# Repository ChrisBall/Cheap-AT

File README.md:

# Cheap AT
 Repository for cheap Assistive Tech and Accessible Music Tech

 Currently seeking help to develop and improve these repositories.

 Switch Hub - Contains files necessary to reproduce an 8-input HID MIDI switch hub, based on the XIAO ESP32S3 dev board. This means you can connect accessibility switches to this box and plug it into your computer, and you'll get musical MIDI data when you press the attached switches.

 Quick Switch - A simple design for a 3D printed accessibility switch (developed in OpenSCAD) that is made of 3 parts: a top; a base; and a PCB. The design is extremely cheap & simple to manufacture, although could stand to be improved; the switch requires different levels of pressure depending on where you press it, and is not especially durable.

 Desired Improvements:
 
 - Multiple switch hub firmware types for different purposes (keyboard/gamepad/joystick emulation) with a simple user interface for configuration, or a single multipurpose firmware with easy configuration.
 - Cheaper hardware for the switch hub - I am currently using a XIAO ESP32S3 as it provides battery management and allows for future wireless/BLE versions, but there may be a cheaper dev board or bespoke hardware.

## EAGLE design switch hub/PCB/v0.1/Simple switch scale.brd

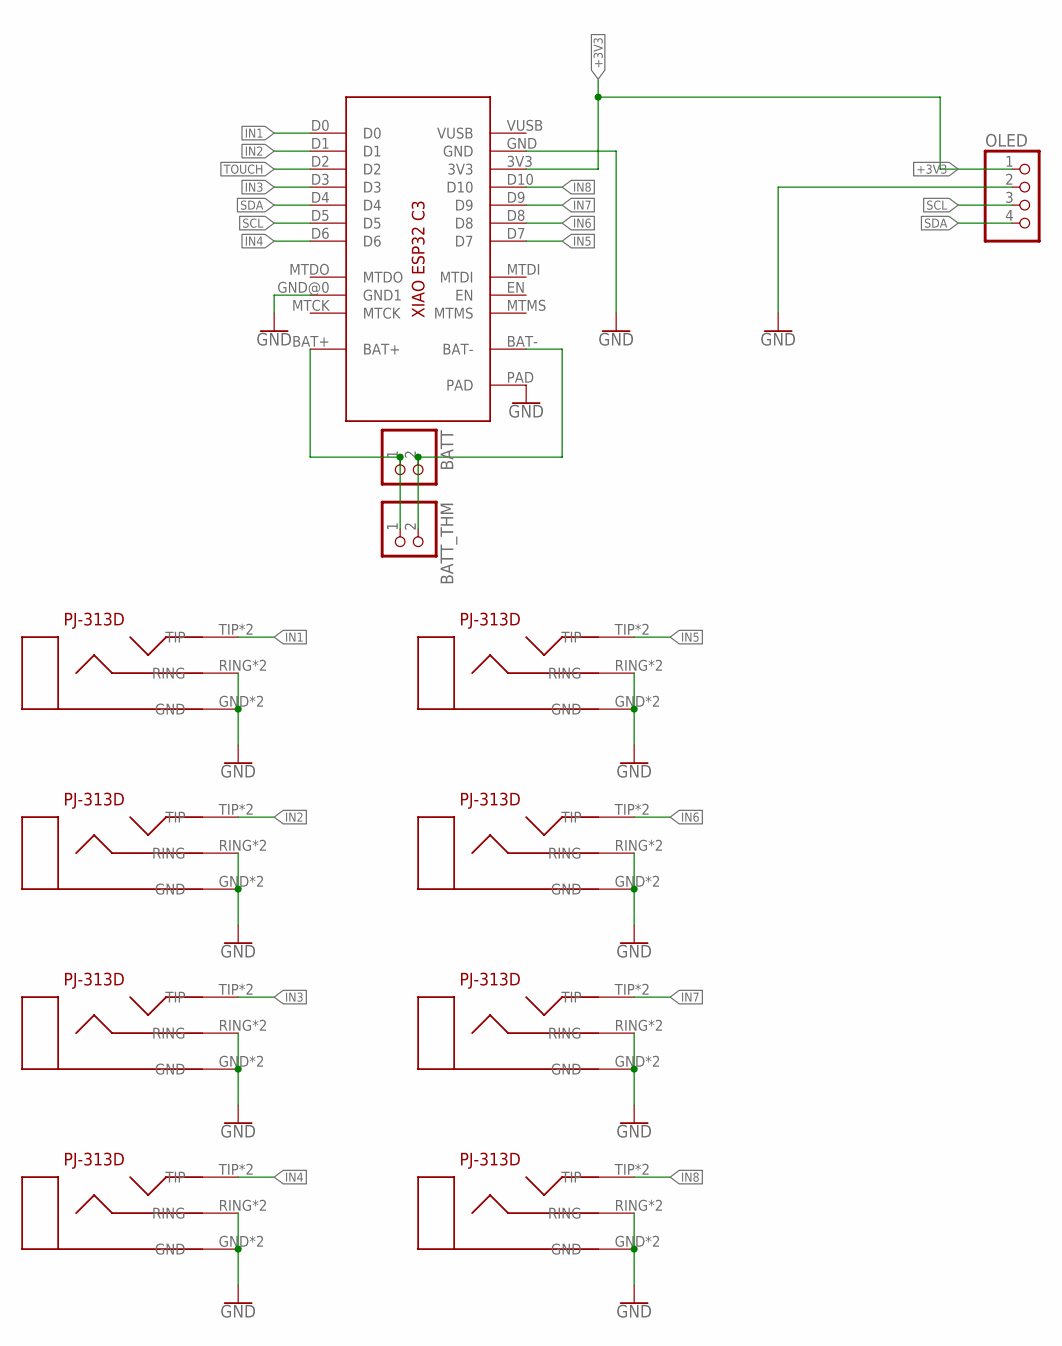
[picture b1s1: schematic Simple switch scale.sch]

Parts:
BATT: JST_2PIN-SMT-RA; JST-PH-2-SMT-RA
BATT_THM: JST_2PIN-THM-RA; JST-PH-2-THM-RA
IN1, IN2, IN3, IN4, IN5, IN6, IN7, IN8: 3.5MM_JACK; PJ-313D-SMT
OLED: HEADER-1X4; 1X04_OVAL
U$1: XIAO_ESP32C3_SMD

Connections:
+3V3: OLED.1, U$1.3V3
GND: IN1.GND, IN1.GND0 (GND), IN1.RING, IN1.RING0 (RING), IN2.GND, IN2.GND0 (GND), IN2.RING, IN2.RING0 (RING), IN3.GND, IN3.GND0 (GND), IN3.RING, IN3.RING0 (RING), IN4.GND, IN4.GND0 (GND), IN4.RING, IN4.RING0 (RING), IN5.GND, IN5.GND0 (GND), IN5.RING, IN5.RING0 (RING), IN6.GND, IN6.GND0 (GND), IN6.RING, IN6.RING0 (RING), IN7.GND, IN7.GND0 (GND), IN7.RING, IN7.RING0 (RING), IN8.GND, IN8.GND0 (GND), IN8.RING, IN8.RING0 (RING), OLED.2, U$1.GND, U$1.GND@0 (GND1), U$1.PAD
IN1: IN1.TIP, IN1.TIP0 (TIP), U$1.D0
IN2: IN2.TIP, IN2.TIP0 (TIP), U$1.D1
IN3: IN3.TIP, IN3.TIP0 (TIP), U$1.D3
IN4: IN4.TIP, IN4.TIP0 (TIP), U$1.D6
IN5: IN5.TIP, IN5.TIP0 (TIP), U$1.D7
IN6: IN6.TIP, IN6.TIP0 (TIP), U$1.D8
IN7: IN7.TIP, IN7.TIP0 (TIP), U$1.D9
IN8: IN8.TIP, IN8.TIP0 (TIP), U$1.D10
unnamed: BATT.1 (2), BATT_THM.1 (2), U$1.BAT+
unnamed: BATT.2 (1), BATT_THM.2 (1), U$1.BAT-
SCL: OLED.3, U$1.D5
SDA: OLED.4, U$1.D4
TOUCH: U$1.D2

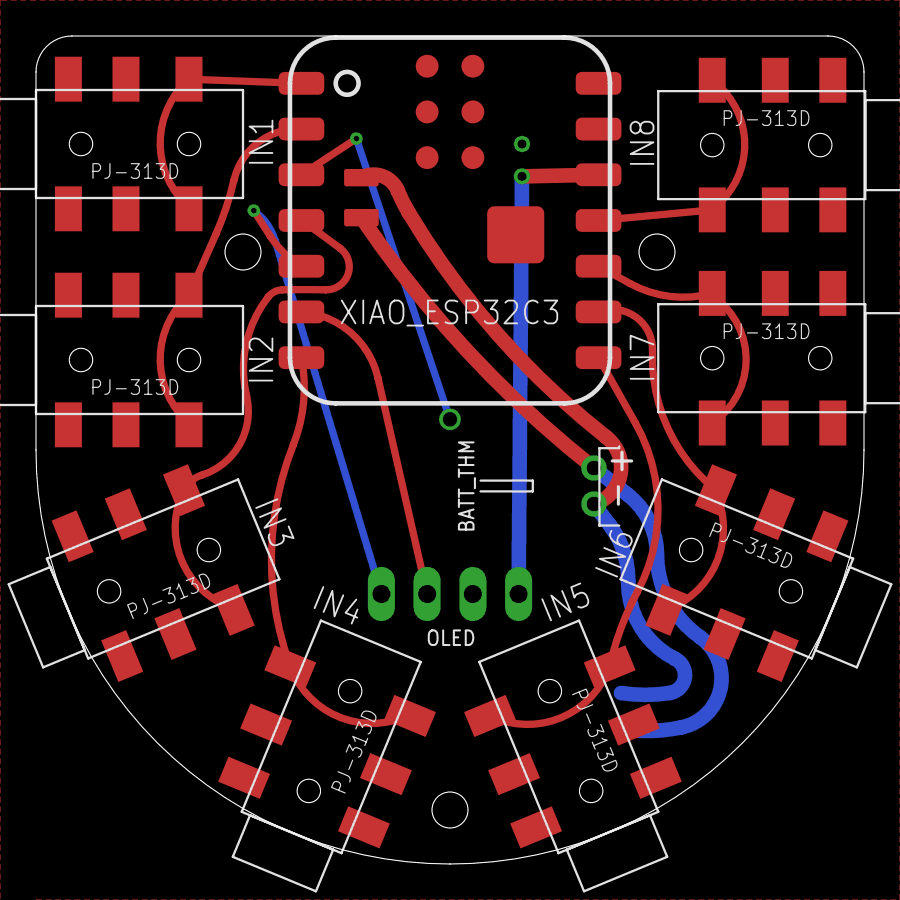
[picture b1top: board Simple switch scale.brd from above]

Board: 2 copper layers, 46.0 x 46.0 mm, 12 parts (1 on the bottom side), 14 nets.

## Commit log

2024-12-04 Added initial files
2026-02-21 Updated all files for mk3 switch
2026-02-21 spelling
2026-03-11 updated with old/new versions

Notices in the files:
parts and their libraries:
microbuilder: This work is placed in the public domain, and may be freely used for commercial and non-commercial work with the following conditions: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
SparkFun-PowerSymbols: Licensing: Creative Commons ShareAlike 4.0 International - https://creativecommons.org/licenses/by-sa/4.0
